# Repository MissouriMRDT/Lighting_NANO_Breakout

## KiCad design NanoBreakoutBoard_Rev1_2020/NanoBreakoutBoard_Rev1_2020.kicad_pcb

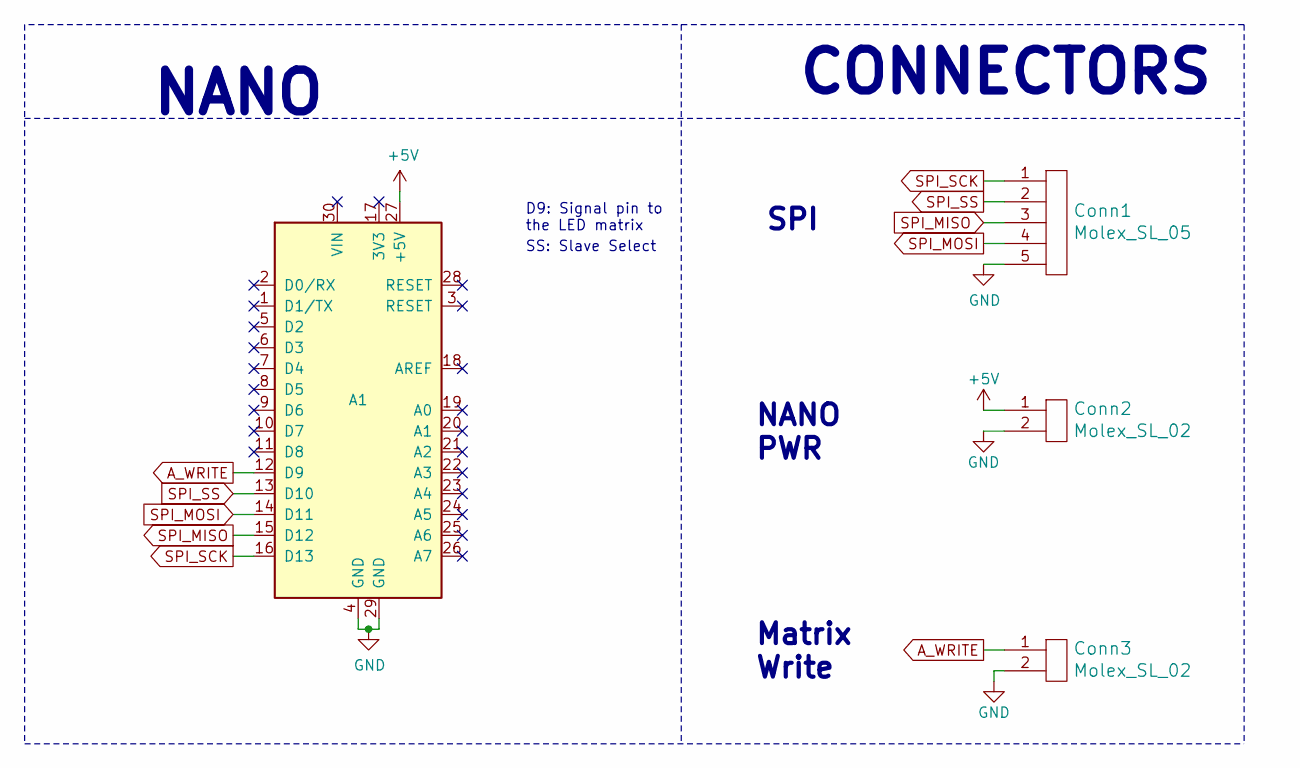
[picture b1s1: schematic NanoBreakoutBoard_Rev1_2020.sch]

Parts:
A1: Arduino_Nano_v3.x; NANO_33_Footprint_SMD_Castell
Conn1: Molex_SL_05; MOLEX_SL_05_Horizontal
Conn2, Conn3: Molex_SL_02; MOLEX_SL_02_Horizontal

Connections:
+5V: A1.27 (+5V), Conn2.1
A_WRITE: A1.12 (D9), Conn3.1
GND: A1.4 (GND), A1.29 (GND), Conn1.5, Conn2.2, Conn3.2
SPI_MISO: A1.15 (D12), Conn1.3
SPI_MOSI: A1.14 (D11), Conn1.4
SPI_SCK: A1.16 (D13), Conn1.1
SPI_SS: A1.13 (D10), Conn1.2

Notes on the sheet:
CONNECTORS
NANO
SPI
D9: Signal pin to the LED matrix
NANO PWR
Matrix Write
SS: Slave Select

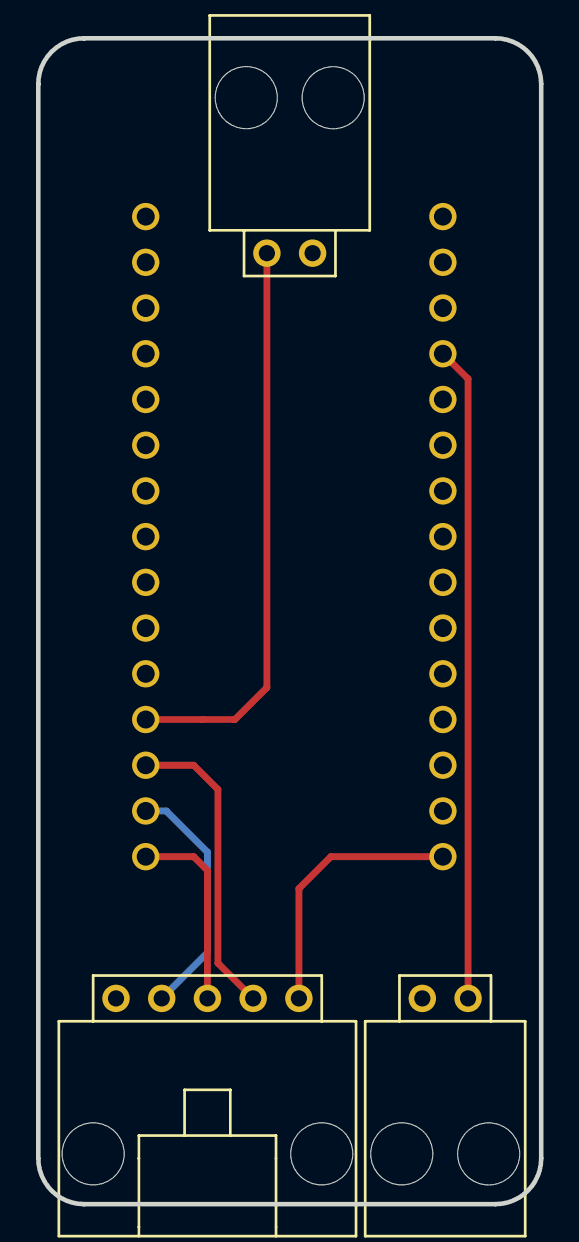
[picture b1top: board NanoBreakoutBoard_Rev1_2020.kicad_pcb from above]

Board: 2 copper layers, 27.9 x 64.8 mm, 4 parts (0 on the bottom side), 7 nets.

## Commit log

2020-03-03 First push
